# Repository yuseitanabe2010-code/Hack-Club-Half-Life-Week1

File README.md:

My project is a USB HUb that has one male USB A connector to plg into a laptop or PC, which then splits off into 2 USB A female and 2 USB C femlae ports can you can plu things into. I made it because I'm tired of my chromebook not having enough ports to plug in accessories and such. Also, it doesn't have any USB C ports. 
The overall design of this is pretty simple, there is 1 male usb a connector and 2 usb a female connectors, 2 usb c femlae connectors. These all sit on a pcb that I designed, all connected to a usb controller that basically takes the incoming data and power and diverts it to the 4 output ports. 
The 12MHz keeps the necessary timing consistent in order for the data to be synchronized.
The decoupling capacitators filter out electrical noise, smooth out voltage spikes, and ensure the SL2.1A chip gets stable power during data spikes.
The pull up/down resistors configure specific control pins on the hub controller to fixed logic states. This allows the chips to handle port power control correctly.

This is the schematic of the hub.

This is the finsihed PCB design.

[SL2.1A_USB_Hub_BOM.csv](https://github.com/user-attachments/files/33315746/SL2.1A_USB_Hub_BOM.csv)
This is the 3d model of the PCB.

BOM with link to suppliers

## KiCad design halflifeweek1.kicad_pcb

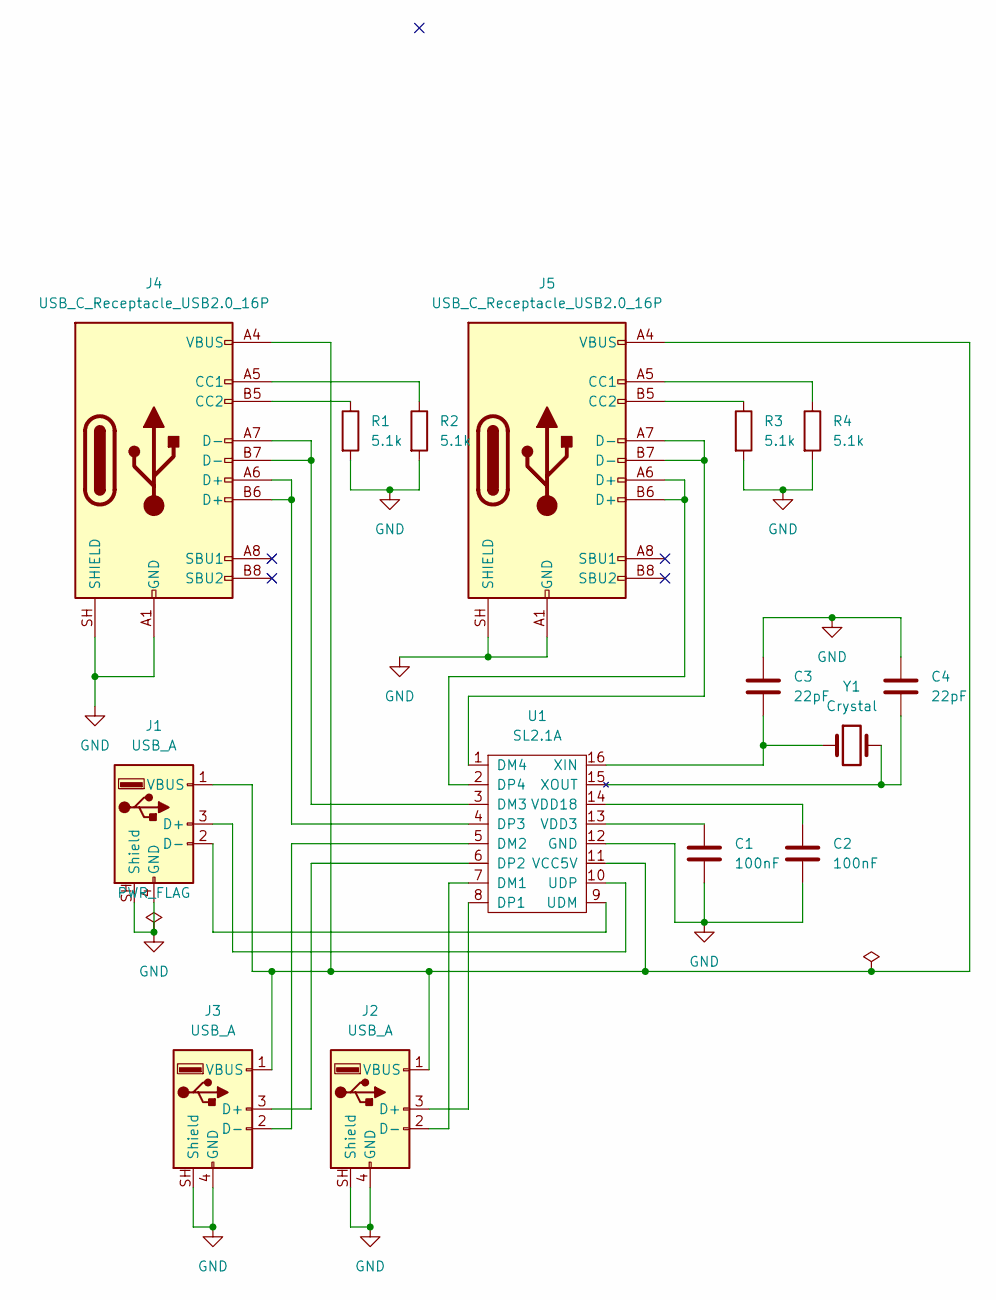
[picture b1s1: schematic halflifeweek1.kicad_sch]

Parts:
C1, C2: 100nF; C_0805_2012Metric_Pad1.18x1.45mm_HandSolder
C3, C4: 22pF; C_0805_2012Metric_Pad1.18x1.45mm_HandSolder
J1: USB_A; USB_A_CNCTech_1001-011-01101_Horizontal
J2, J3: USB_A; USB_A_Molex_67643_Horizontal
J4, J5: USB_C_Receptacle_USB2.0_16P; USB_C_Receptacle_GCT_USB4105-xx-A_16P_TopMnt_Horizontal
R1, R2, R3, R4: 5.1k; R_0805_2012Metric_Pad1.20x1.40mm_HandSolder
U1: SL2.1A; SOIC-16_3.9x9.9mm_P1.27mm
Y1: Crystal; Crystal_HC49-U-3Pin_Vertical

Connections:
GND: C1.2, C2.2, C3.2, C4.1, J1.4 (GND), J1.SH (Shield), J2.4 (GND), J2.SH (Shield), J3.4 (GND), J3.SH (Shield), J4.A1 (GND), J4.A12 (GND), J4.B1 (GND), J4.B12 (GND), J4.SH (SHIELD), J5.A1 (GND), J5.A12 (GND), J5.B1 (GND), J5.B12 (GND), J5.SH (SHIELD), R1.2, R2.2, R3.2, R4.2, U1.12 (GND)
unnamed: C4.2, U1.15 (XOUT), Y1.2
unnamed: J1.3 (D+), U1.10 (UDP)
unnamed: J1.2 (D-), U1.9 (UDM)
unnamed: J1.1 (VBUS), J2.1 (VBUS), J3.1 (VBUS), J4.A4 (VBUS), J4.A9 (VBUS), J4.B4 (VBUS), J4.B9 (VBUS), J5.A4 (VBUS), J5.A9 (VBUS), J5.B4 (VBUS), J5.B9 (VBUS), U1.11 (VCC5V)
unnamed: J2.3 (D+), U1.8 (DP1)
unnamed: J2.2 (D-), U1.7 (DM1)
unnamed: J3.3 (D+), U1.6 (DP2)
unnamed: J3.2 (D-), U1.5 (DM2)
unnamed: J4.A5 (CC1), R2.1
unnamed: J4.B5 (CC2), R1.1
unnamed: J5.A5 (CC1), R4.1
unnamed: J5.B5 (CC2), R3.1
unnamed: J4.A7 (D-), J4.B7 (D-), U1.3 (DM3)
unnamed: J5.A7 (D-), J5.B7 (D-), U1.1 (DM4)
unnamed: J4.A6 (D+), J4.B6 (D+), U1.4 (DP3)
unnamed: J5.A6 (D+), J5.B6 (D+), U1.2 (DP4)
unnamed: C1.1, U1.13 (VDD3)
unnamed: C2.1, U1.14 (VDD18)
unnamed: C3.1, U1.16 (XIN), Y1.1

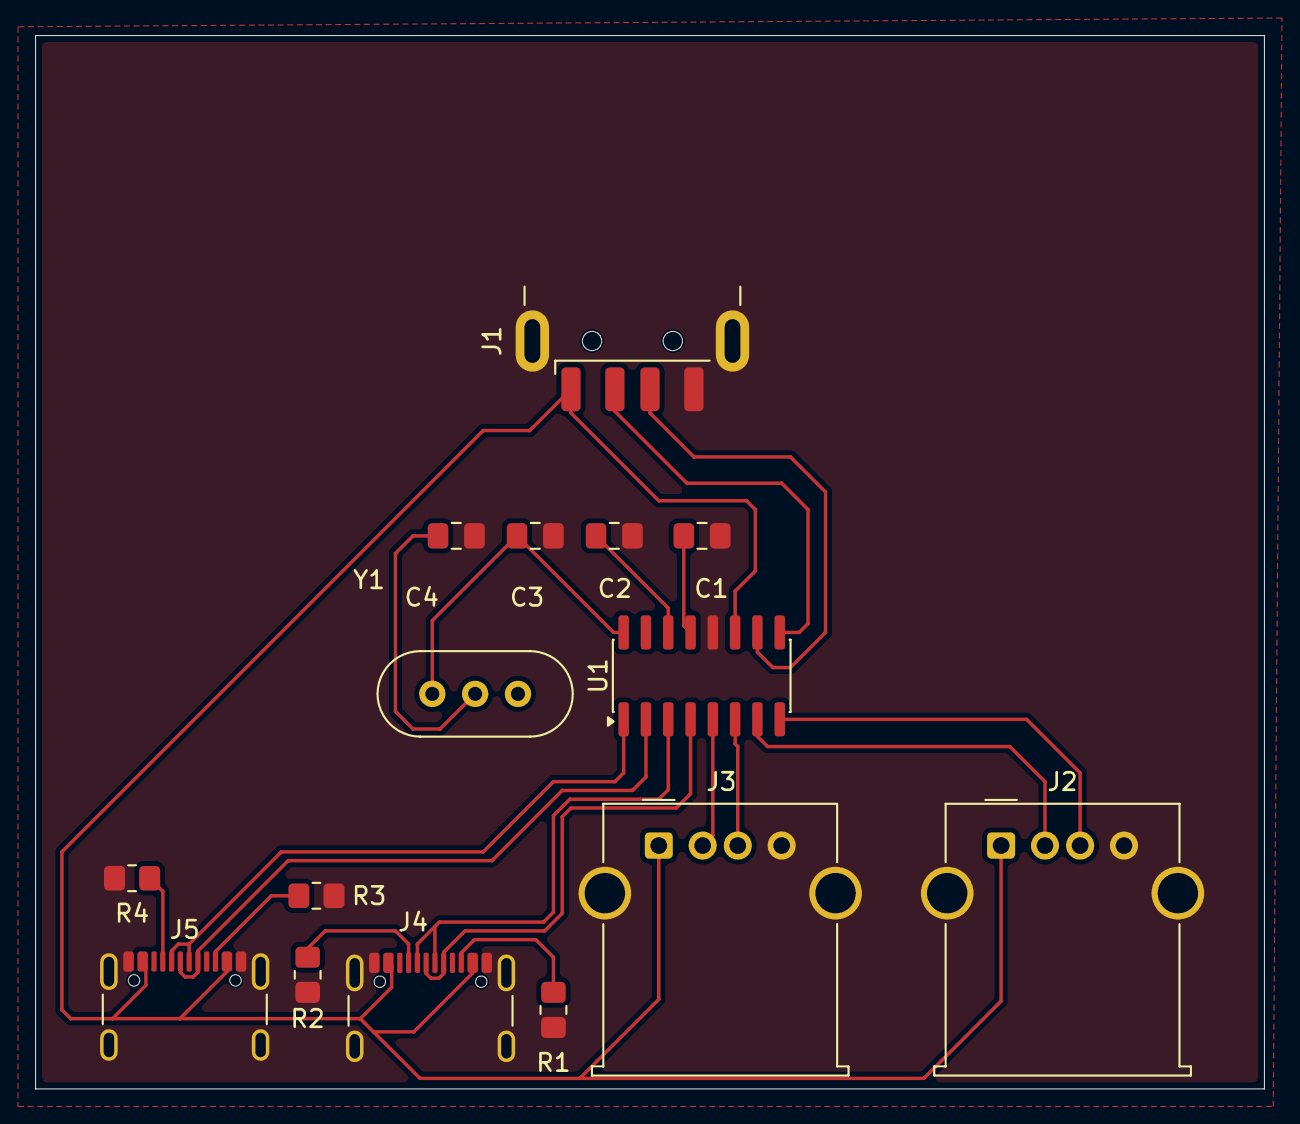
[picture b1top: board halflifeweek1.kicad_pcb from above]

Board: 2 copper layers, 70.0 x 60.0 mm, 15 parts (0 on the bottom side), 20 nets.
